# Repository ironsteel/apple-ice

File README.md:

# Apple-iCE

## Apple II peripheral card prototype which aims to be multi purpose

# Work in progess

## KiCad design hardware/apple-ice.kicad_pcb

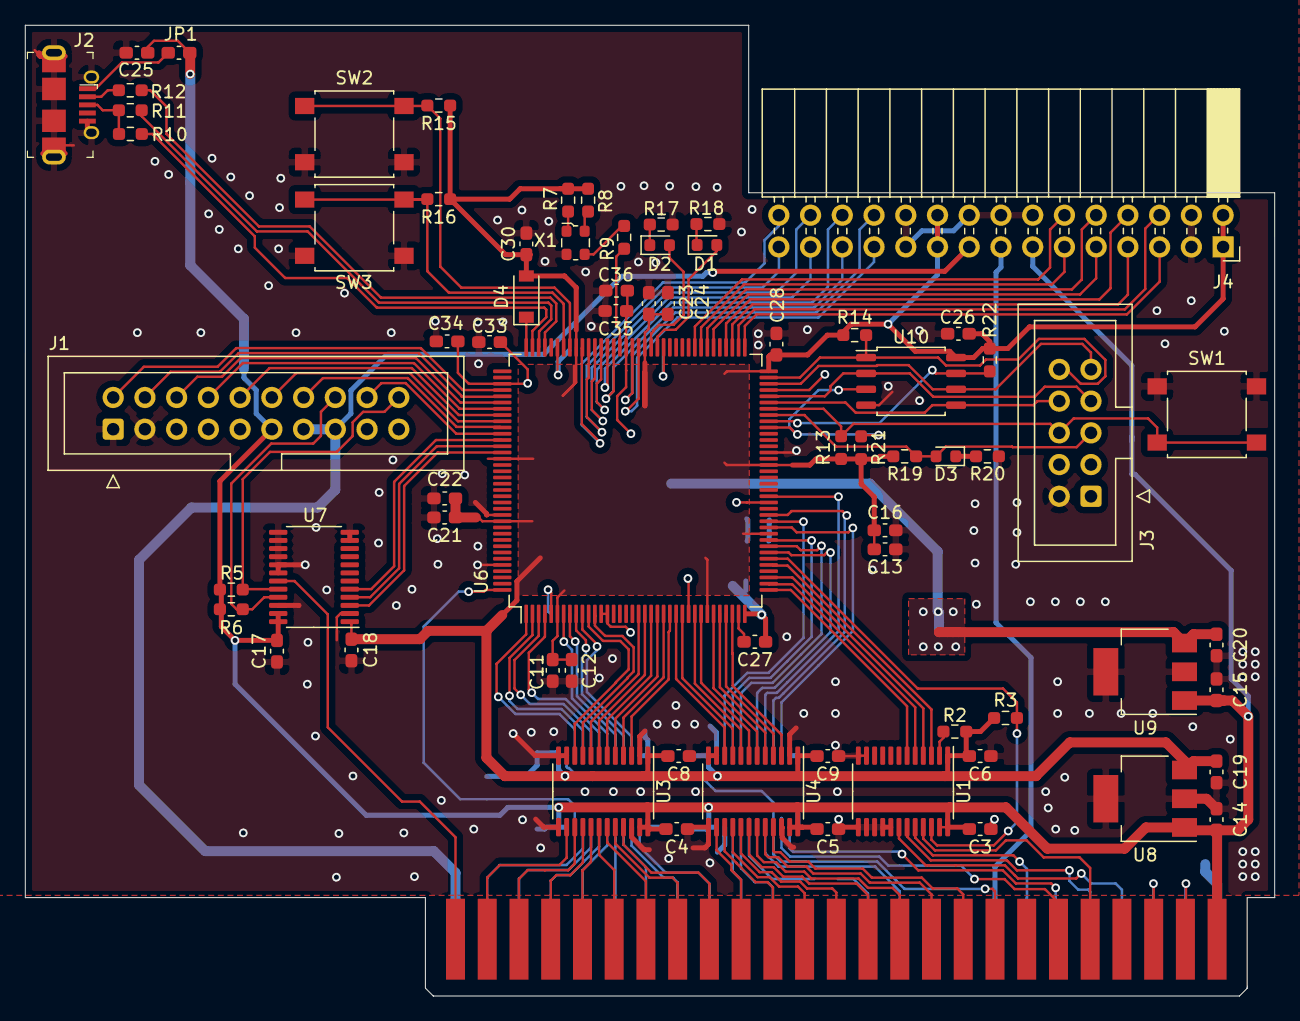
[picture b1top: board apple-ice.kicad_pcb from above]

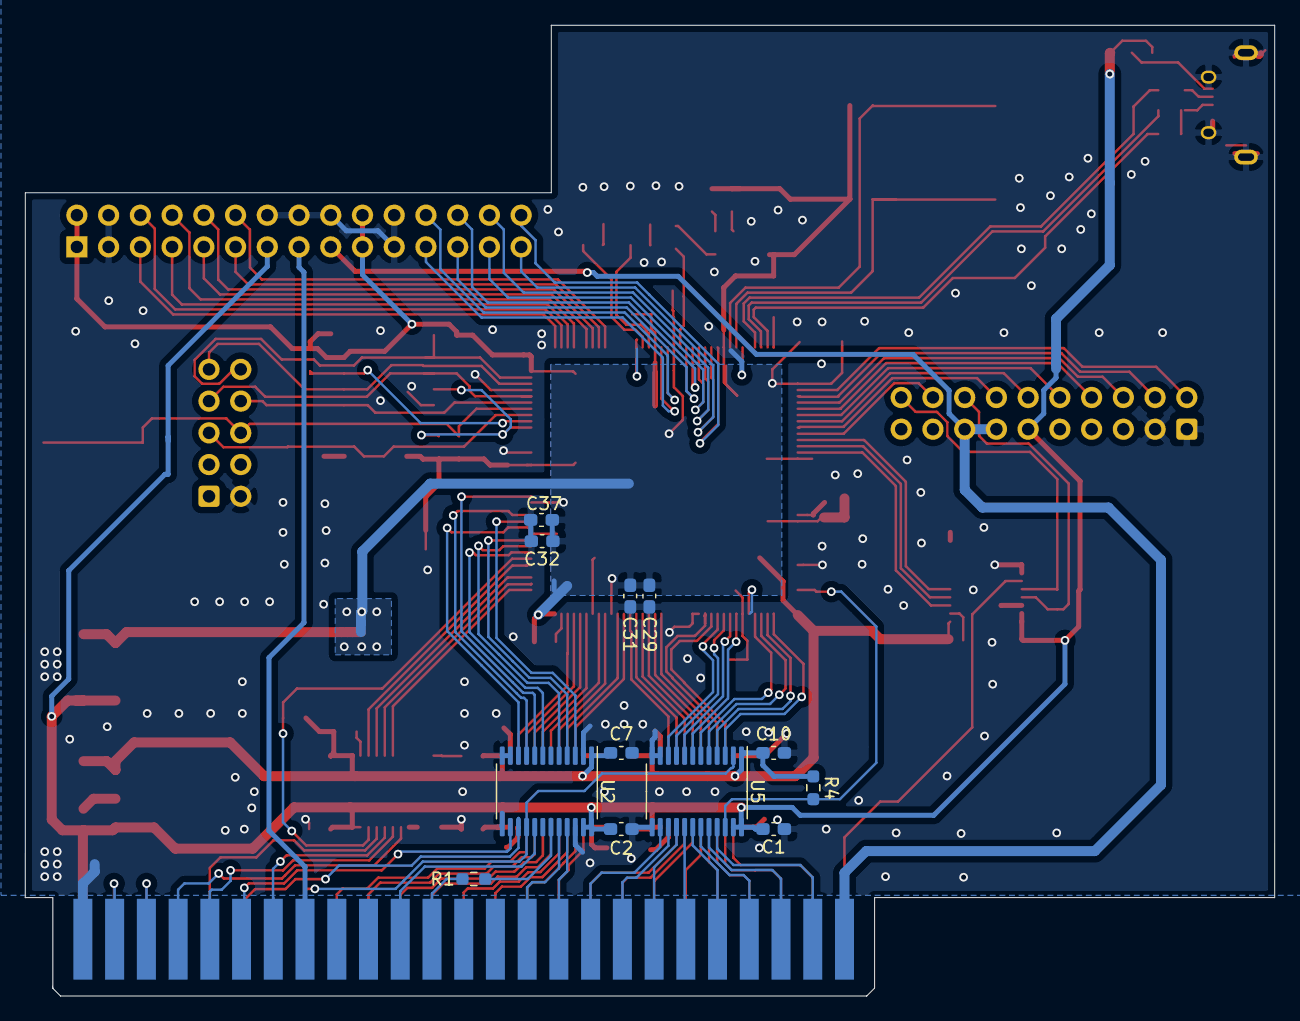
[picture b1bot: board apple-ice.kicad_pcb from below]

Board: 2 copper layers, 100.0 x 77.7 mm, 83 parts (12 on the bottom side), 139 nets.

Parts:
C1, C2, C3, C4, C5, C6, C7, C8, C9, C10, C17, C18: 0.1uF; C_0603_1608Metric_Pad1.08x0.95mm_HandSolder
C11, C13, C21, C23, C29, C32, C33, C34: 1u; C_0603_1608Metric_Pad1.08x0.95mm_HandSolder
C12, C16, C22, C24, C25, C26, C27, C28, C30, C31, C35, C36, C37: 100n; C_0603_1608Metric_Pad1.08x0.95mm_HandSolder
C14, C15, C19, C20: 1uF; C_0603_1608Metric_Pad1.08x0.95mm_HandSolder
D1, D2, D3: LED; LED_0603_1608Metric
D4: 1N5819; D_SOD-123
J1: TO_SP_DRIVE; IDC-Header_2x10_P2.54mm_Vertical
J2: USB_B_Micro; MOLEX-0475890001
J3: SPI_FLASH_PROG; IDC-Header_2x05_P2.54mm_Vertical
J4: Conn_02x15_Odd_Even; PinSocket_2x15_P2.54mm_Horizontal
JP1: J_USB_5V; C_0603_1608Metric_Pad1.08x0.95mm_HandSolder
P1: A2Bus-apple2; A2-50PIN-MINI
R1: 390; R_0603_1608Metric_Pad0.98x0.95mm_HandSolder
R2, R3, R4, R5, R6: 22k; R_0603_1608Metric_Pad0.98x0.95mm_HandSolder
R7, R13, R14, R15, R16, R21, R22: 10k; R_0603_1608Metric_Pad0.98x0.95mm_HandSolder
R8, R9: 10; R_0603_1608Metric_Pad0.98x0.95mm_HandSolder
R10: 1k5; R_0603_1608Metric_Pad0.98x0.95mm_HandSolder
R11, R12, R20: 22; R_0603_1608Metric_Pad0.98x0.95mm_HandSolder
R17, R18, R19: 2k2; R_0603_1608Metric_Pad0.98x0.95mm_HandSolder
SW1, SW2, SW3: SW_Push; SW_SPST_B3S-1000
U1, U2, U3, U4, U5, U7: SN74LVC8T245PW; TSSOP-24_4.4x7.8mm_P0.65mm
U6: ICE40HX1K-TQ144; TQFP-144_20x20mm_P0.5mm
U8: MCP1703A-3302_SOT223; SOT-223-3_TabPin2
U9: MCP1703A-1202_SOT223; SOT-223-3_TabPin2
U10: W25Q16JVSS; SOIC-8_5.23x5.23mm_P1.27mm
X1: ECS-2520MV-xxx-xx; Oscillator_SMD_ECS_2520MV-xxx-xx-4Pin_2.5x2.0mm

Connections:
+1V2: C20.1, C27.1, C29.1, C31.1, C32.1, C33.1, C34.1, C35.1, C36.1, C37.1, U6.27, U6.36, U6.51, U6.92, U6.111, U9.3
+3.3V: C6.2, C7.2, C8.2, C9.2, C10.2, C11.1, C12.1, C13.1, C16.1, C18.2, C19.1, C21.1, C22.1, C23.1, C24.1, C26.1, C28.1, C30.1, D4.2, J4.1, J4.2, J4.19, J4.20, R2.1, R3.1, R4.1, R7.1, R8.1, R13.1, R14.1, R15.1, R16.1, R19.1, R21.1, R22.1, U1.1, U2.1, U3.1, U4.1, U5.1, U6.6, U6.30, U6.46, U6.57, U6.72, U6.89, U6.100, U6.123, U6.133, U7.1, U8.3, U10.8
+5V: C1.2, C2.2, C3.2, C4.2, C5.2, C14.1, C15.1, C17.2, C25.2, J1.11, J4.13, JP1.1, P1.25, R5.1, R6.1, U1.23, U1.24, U2.23, U2.24, U3.23, U3.24, U4.23, U4.24, U5.23, U5.24, U7.23, U7.24, U8.1, U9.1
+12V: J1.13, J1.15, J4.17, P1.50
-12V: J4.15, P1.33
/7M: P1.36, U2.17
/7M_33: U2.7, U6.43
/16Mhz: R9.1, U6.93
/A0: P1.02, U3.14
/A0_33: U3.10, U6.11
/A1: P1.03, U3.15
/A1_33: U3.9, U6.12
/A2: P1.04, U3.16
/A2_33: U3.8, U6.19
/A3: P1.05, U3.17
/A3_33: U3.7, U6.20
/A4: P1.06, U3.18
/A4_33: U3.6, U6.21
/A5: P1.07, U3.19
/A5_33: U3.5, U6.22
/A6: P1.08, U3.20
/A6_33: U3.4, U6.23
/A7: P1.09, U3.21
/A7_33: U3.3, U6.24
/A8: P1.10, U4.14
/A8_33: U4.10, U6.25
/A9: P1.11, U4.15
/A9_33: U4.9, U6.26
/A10: P1.12, U4.16
/A10_33: U4.8, U6.28
/A11: P1.13, U4.17
/A11_33: U4.7, U6.29
/A12: P1.14, U4.18
/A12_33: U4.6, U6.31
/A13: P1.15, U4.19
/A13_33: U4.5, U6.32
/A14: P1.16, U4.20
/A14_33: U4.4, U6.33
/A15: P1.17, U4.21
/A15_33: U4.3, U6.34
/BTN1: R15.2, SW2.1, U6.101
/BTN2: R16.2, SW3.1, U6.102
/D0: P1.49, U5.21
/D0_33: U5.3, U6.1
/D1: P1.48, U5.20
/D1_33: U5.4, U6.2
/D2: P1.47, U5.19
/D2_33: U5.5, U6.3
/D3: P1.46, U5.18
/D3_33: U5.6, U6.4
/D4: P1.45, U5.17
/D4_33: U5.7, U6.7
/D5: P1.44, U5.16
/D5_33: U5.8, U6.8
/D6: P1.43, U5.15
/D6_33: U5.9, U6.9
/D7: P1.42, U5.14
/D7_33: U5.10, U6.10
/LED1: D1.2, U6.87
/LED2: D2.2, U6.88
/PH0: J1.2, U6.112
/PH1: J1.4, U6.113
/PH2: J1.6, U6.114
/PH3: J1.8, U6.115
/PHI0: P1.40, U2.20
/PHI0_33: U2.4, U6.45
/PMOD1_0: J4.23, U6.90
/PMOD1_1: J4.24, U6.91
/PMOD1_2: J4.25, U6.94
/PMOD1_3: J4.26, U6.95
/PMOD1_4: J4.27, U6.96
/PMOD1_5: J4.28, U6.97
/PMOD1_6: J4.29, U6.98
/PMOD1_7: J4.30, U6.99
/PMOD_0: J4.5, U6.73
/PMOD_1: J4.6, U6.74
/PMOD_2: J4.7, U6.75
/PMOD_3: J4.8, U6.76
/PMOD_4: J4.9, U6.78
/PMOD_5: J4.10, U6.79
/PMOD_6: J4.11, U6.80
/PMOD_7: J4.12, U6.81
/Q3: R1.1, U2.19
/Q3_33: U2.5, U6.44
/RDDATA: J1.16, R6.2, U7.21
/RDDATA_33: U6.122, U7.3
/RW: P1.18, U2.16, U5.2
/RW_33: U2.8, U6.52
/SEL: J1.12, U6.117
/SENSE: J1.20, R5.2, U7.20
/SENSE_33: U6.121, U7.4
/USB_N: R12.1, U6.105
/USB_P: R11.1, U6.106
/USB_PU: R10.2, U6.107
/WRDATA: J1.18, U6.119
/iC40_SDI: J3.7, U6.68, U10.2
/iC40_SDO: J3.8, U6.67, U10.5
/iCE40_CDONE: D3.2, J3.5, R19.2, U6.65
/iCE40_SCK: J3.9, U6.70, U10.6
/~DEVSEL: P1.41, U2.21
/~DEVSEL_33: U2.3, U6.48
/~D_OE: R4.2, U5.22, U6.144
/~ENABLE: J1.14, U6.118
/~FLASH_HOLD(~IO4): R22.2, U6.64, U10.7
/~FLASH_WP(~IO3): R21.2, U6.63, U10.3
/~INH: U1.4, U6.39
/~IOSEL: P1.01, U7.19
/~IOSEL_33: U6.120, U7.5
/~IOSTROBE: P1.20, U2.15
/~IOSTROBE_33: U2.9, U6.49
/~IRQ: U1.5, U6.38
/~NMI: U1.6, U6.37
/~RDY: U1.3, U6.41
/~RES: P1.31, U2.14
/~RES_33: U2.10, U6.47
/~WREQ: J1.10, U6.116
/~iCE40_CRESET: J3.6, R13.2, SW1.2, U6.66
/~iCE40_CS: J3.10, R14.2, U6.71, U10.1
GND: C1.1, C2.1, C3.1, C4.1, C5.1, C6.1, C7.1, C8.1, C9.1, C10.1, C11.2, C12.2, C13.2, C14.2, C15.2, C16.2, C17.1, C18.1, C19.2, C20.2, C21.2, C22.2, C23.2, C24.2, C25.1, C26.2, C28.2, C29.2, C30.2, C31.2, C32.2, C33.2, C34.2, C35.2, C36.2, C37.2, J1.1, J1.3, J2.5, J2.6, J3.2, J4.3, J4.4, J4.14, J4.16, J4.18, J4.21, J4.22, P1.26, R17.1, R18.1, R20.2, SW1.1, SW2.2, SW3.2, U1.11, U1.12, U1.13, U1.14, U1.15, U1.16, U1.17, U2.2, U2.11, U2.12, U2.13, U2.22, U3.2, U3.11, U3.12, U3.13, U3.22, U4.2, U4.11, U4.12, U4.13, U4.22, U5.11, U5.12, U5.13, U6.5, U6.13, U6.14, U6.59, U6.69, U6.86, U6.103, U6.132, U6.140, U7.2, U7.11, U7.12, U7.13, U7.14, U7.15, U7.16, U7.17, U7.18, U7.22, U8.2, U9.2, U10.4, X1.2
unnamed: C27.2, U6.35
unnamed: D1.1, R18.2
unnamed: D2.1, R17.2
unnamed: D3.1, R20.1
unnamed: D4.1, U6.108
unnamed: J2.1, JP1.2
unnamed: J2.2, R12.2
unnamed: J2.3, R10.1, R11.2
unnamed: P1.21, U1.21
unnamed: P1.23, P1.28
unnamed: P1.24, P1.27
unnamed: P1.29, U1.18
unnamed: P1.30, U1.19
unnamed: P1.32, U1.20
unnamed: P1.37, R1.2
unnamed: R2.2, U1.2
unnamed: R3.2, U1.22, U6.42
unnamed: R7.2, X1.1
unnamed: R8.2, X1.4
unnamed: R9.2, X1.3

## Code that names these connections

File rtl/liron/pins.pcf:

set_io clk_16  93
set_io addr[0]  11
set_io addr[1]  12
set_io addr[2]  19
set_io addr[3]  20
set_io addr[4]  21
set_io addr[5]  22
set_io addr[6]  23
set_io addr[7]  24
set_io addr[8]  25
set_io addr[9]  26
set_io addr[10] 28
set_io addr[11] 29

set_io data[0]  1
set_io data[1]  2
set_io data[2]  3
set_io data[3]  4
set_io data[4]  7
set_io data[5]  8
set_io data[6]  9
set_io data[7]  10

set_io q3 44
set_io _reset 47
set_io fclk 43
set_io rw 52
set_io _iosel 120
set_io _iostrobe 56

set_io _en245 144

set_io phase[0] 112
set_io phase[1] 113
set_io phase[2] 114
set_io phase[3] 115

set_io _wrreq 116
set_io select 117
set_io _enbl1 118
set_io wrdata 119
set_io sense 121
set_io rddata 122
set_io _devsel 48

set_io btn    101

set_io _nmi 37
set_io _irq 38
set_io _inh 39
set_io _rdy 41

set_io test[0] 73
set_io test[1] 74
set_io test[2] 75
set_io test[3] 76
set_io test[4] 78
set_io test[5] 79
set_io test[6] 80
set_io test[7] 81

set_io phi0 45

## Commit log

2021-05-08 Initial commit
    Initial kicad project
2021-05-08 Add footprints for ice40 FPGA and apple II bus connector
2021-05-15 Add apple 2 bus/cardedge symbol
2021-05-17 Symbols and footprints
2021-05-27 Apple II connections part complete
    Edge cuts for board, initial placement of buffers
2021-06-06 FPGA programming and power
    Reorginize schematic
    Add more footprints and symbols
2021-06-08 Begin initial placement and routing
2021-06-08 Add license and initial readme
2021-07-03 Initial placement V2
2021-07-07 Add new micro USB footprint
2021-07-08 More schematic tweaking for easier routing
2021-07-13 More routing, 80% finished
2021-07-18 Finish routing
2021-07-18 Remove some vias
2021-07-20 Add 2x15 pin header
2021-08-01 Route double pmod header
2021-08-01 Add 5, 12 and -12 power rails to pmod connection
2021-08-01 Add some useful text to the PCB
2021-08-01 Move via out of silk screen text
2021-08-15 Add interective bom
2021-08-28 Initial skeleton for super serial card clone
2021-10-15 Rev 0.2
2021-10-15 Move io_strobe signal to an FPGA pin that is not shared with the PLL
2021-12-27 Liron clone based on the design of Steve Chamberlin from BMOW
    With some minor tweaks so it works on my apple II clones (pravetz)
